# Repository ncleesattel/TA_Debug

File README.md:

# TA_Debug
PCB designed with KiCad to make a debug main unit for TeenAstro V3 testing.  
I haven't built my own debug platform yet, so I would encourage you to wait for my feedback.  

## internal connectors
The pcb is intended to accommodate:
* TMC5160 for RA, DEC and Focusser
  * the TMC5160 can either be connected via step/dir or SPI 
* 16 MHz oscillators for TMC5160
* NEO-M8n GNSS satellite positioning system
* DS3232 RTC
* power is supplied from a DC jack that splits into
  * VCC for steppers (12 - 24V)
  * 5V for legacy SHC
  * 3.3V for everything else
  * CR32 battery
* power is provided by two Traco DC/DC converters

## external connectors
An MCU like ESP32 or Teensy 4.x can be connected through a ribbon cable to a breadboard.  
There are also connectors for an SHC, stepper motors and encoders.  

## pictures

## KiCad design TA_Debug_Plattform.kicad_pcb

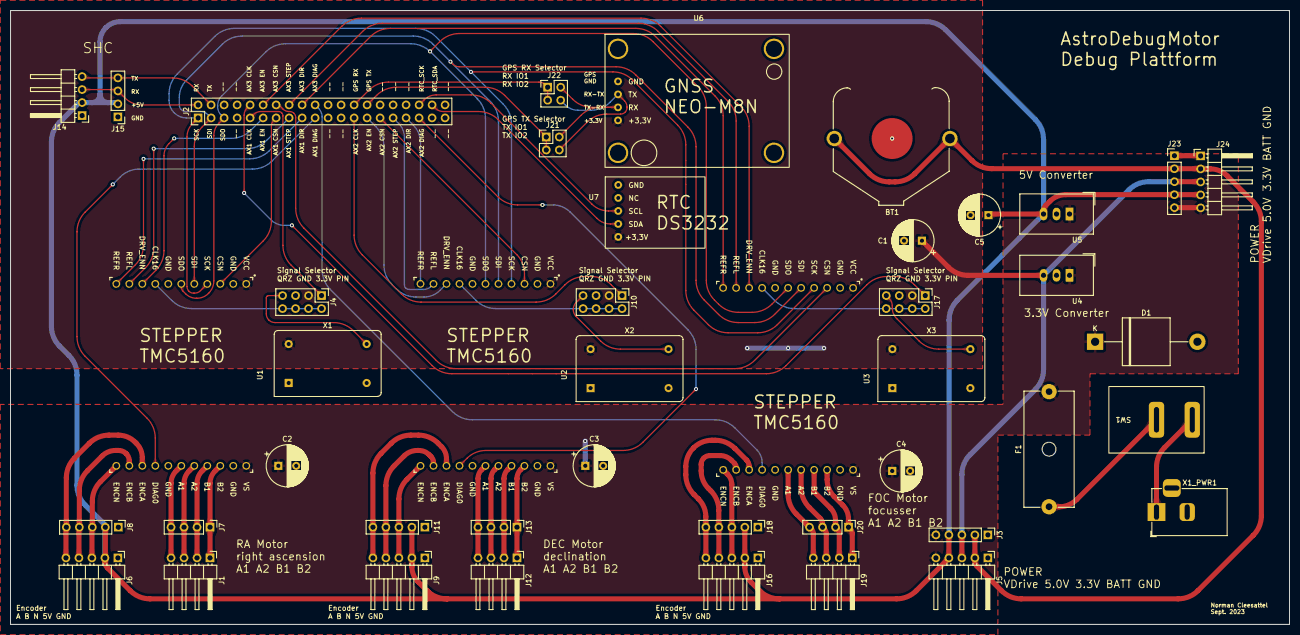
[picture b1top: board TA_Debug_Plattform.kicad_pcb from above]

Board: 2 copper layers, 250.0 x 120.0 mm, 44 parts (0 on the bottom side), 63 nets.

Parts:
BT1: CR2032-BS-6-1; Battery_KZH_20P
C1, C2, C3, C4, C5: 150uF; CP_Radial_D8.0mm_P3.50mm
D1: P600S; D_P600_R-6_P20.00mm_Horizontal
F1: FLINK 4,0A; Fuseholder_Cylinder-5x20mm_Schurter_0031_8201_Horizontal_Op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
J1: Motor A; PinHeader_1x04_P2.54mm_Horizontal
J2: Conn_02x20_Odd_Even; PinHeader_2x20_P2.54mm_Vertical
J3, J8, J11, J18, J23: Conn_01x05; PinHeader_1x05_P2.54mm_Vertical
J4: AX1 CLK SEL; PinHeader_2x04_P2.54mm_Vertical
J5, J6, J9, J16, J24: Conn_01x05; PinHeader_1x05_P2.54mm_Horizontal
J7: Motor A; PinHeader_1x04_P2.54mm_Vertical
J10: AX2 CLK SEL; PinHeader_2x04_P2.54mm_Vertical
J12: Motor B; PinHeader_1x04_P2.54mm_Horizontal
J13: Motor B; PinHeader_1x04_P2.54mm_Vertical
J14: SHC; PinHeader_1x04_P2.54mm_Horizontal
J15: SHC; PinHeader_1x04_P2.54mm_Vertical
J17: AX3 CLK SEL; PinHeader_2x04_P2.54mm_Vertical
J19: Motor C; PinHeader_1x04_P2.54mm_Horizontal
J20: Motor C; PinHeader_1x04_P2.54mm_Vertical
J21, J22: Conn_02x02_Odd_Even; PinHeader_2x02_P2.54mm_Vertical
SW1: SW_SPST; Marquart
U1, U2, U3: TMC5160-BOB; 22pin1,5x1,1-BOB
U4, U5: TSR_2-2450; Converter_DCDC_TRACO_TSR-2_THT
U6: NEO-M8n-GPS
U7: DS3232
X1, X2, X3: ACO-16MHz; Oscillator_DIP-14
X1_PWR1: Barrel_Jack_MountingPin; BarrelJack_Horizontal

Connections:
+3.3V: C1.1, J3.3, J4.3, J5.3, J10.3, J17.3, J23.3, J24.3, U1.1 (VCC-(3.3V/5V)), U2.1 (VCC-(3.3V/5V)), U3.1 (VCC-(3.3V/5V)), U4.3 (Vout), U6.4 (+3,3V), U7.1 (+3,3V), X1.14 (Vcc), X2.14 (Vcc), X3.14 (Vcc)
+5V: C5.1, J3.4, J5.4, J6.2, J8.2, J9.2, J11.2, J14.2, J15.2, J16.2, J18.2, J23.4, J24.4, U5.3 (Vout)
+BATT: BT1.1 (+), J3.2, J5.2, J23.2, J24.2
/AX1_A1: J1.4, J7.4, U1.17 (A1)
/AX1_A2: J1.3, J7.3, U1.16 (A2)
/AX1_B1: J1.2, J7.2, U1.15 (B1)
/AX1_B2: J1.1, J7.1, U1.14 (B2)
/AX1_CLK: J2.9, J4.1
/AX1_CSN: J2.13, U1.3 (CSN)
/AX1_DIAG: J2.19, U1.19 (DIAGO)
/AX1_DIR: J2.17, U1.11 (REFR)
/AX1_EN: J2.11, U1.9 (DRV_ENN)
/AX1_ENCA: J6.5, J8.5, U1.20 (ENCA)
/AX1_ENCB: J6.4, J8.4, U1.21 (ENCB)
/AX1_ENCN: J6.3, J8.3, U1.22 (ENCN)
/AX1_STEP: J2.15, U1.10 (REFL)
/AX2_A1: J12.4, J13.4, U2.17 (A1)
/AX2_A2: J12.3, J13.3, U2.16 (A2)
/AX2_B1: J12.2, J13.2, U2.15 (B1)
/AX2_B2: J12.1, J13.1, U2.14 (B2)
/AX2_CLK: J2.25, J10.1
/AX2_CSN: J2.29, U2.3 (CSN)
/AX2_DIAG: J2.35, U2.19 (DIAGO)
/AX2_DIR: J2.33, U2.11 (REFR)
/AX2_EN: J2.27, U2.9 (DRV_ENN)
/AX2_ENCA: J9.5, J11.5, U2.20 (ENCA)
/AX2_ENCB: J9.4, J11.4, U2.21 (ENCB)
/AX2_ENCN: J9.3, J11.3, U2.22 (ENCN)
/AX2_STEP: J2.31, U2.10 (REFL)
/AX3_A1: J19.4, J20.4, U3.17 (A1)
/AX3_A2: J19.3, J20.3, U3.16 (A2)
/AX3_B1: J19.2, J20.2, U3.15 (B1)
/AX3_B2: J19.1, J20.1, U3.14 (B2)
/AX3_CLK: J2.10, J17.1
/AX3_CSN: J2.14, U3.3 (CSN)
/AX3_DIAG: J2.20, U3.19 (DIAGO)
/AX3_DIR: J2.18, U3.11 (REFR)
/AX3_EN: J2.12, U3.9 (DRV_ENN)
/AX3_ENCA: J16.5, J18.5, U3.20 (ENCA)
/AX3_ENCB: J16.4, J18.4, U3.21 (ENCB)
/AX3_ENCN: J16.3, J18.3, U3.22 (ENCN)
/AX3_STEP: J2.16, U3.10 (REFL)
/GPS_RX: J2.26, J22.1, J22.3
/GPS_TX: J2.28, J21.1, J21.3
/IO1 GPS: J21.2, J22.2, U6.3 (RX)
/IO2 GPS: J21.4, J22.4, U6.2 (TX)
/RTC_SCK: J2.36, U7.3 (SCK)
/RTC_SDA: J2.38, U7.2 (SDA)
/RX: J2.2, J14.3, J15.3
/SCK: J2.1, U1.4 (SCK), U2.4 (SCK), U3.4 (SCK)
/SDI: J2.3, U1.5 (SDI), U2.5 (SDI), U3.5 (SDI)
/SDO: J2.5, U1.6 (SDO), U2.6 (SDO), U3.6 (SDO)
/TX: J2.4, J14.4, J15.4
GND: BT1.2 (-), C1.2, C2.2, C3.2, C4.2, C5.2, D1.2 (A), J3.1, J4.5, J5.1, J6.1, J8.1, J9.1, J10.5, J11.1, J14.1, J15.1, J16.1, J17.5, J18.1, J23.1, J24.1, U1.2 (GND), U1.7 (GND), U1.13 (GND), U1.18 (GND), U2.2 (GND), U2.7 (GND), U2.13 (GND), U2.18 (GND), U3.2 (GND), U3.7 (GND), U3.13 (GND), U3.18 (GND), U4.2 (GND), U5.2 (GND), U6.1 (GND), U6.5 (GND), U7.4 (NC), U7.5 (GND), X1.7 (GND), X1_PWR1.2, X2.7 (GND), X3.7 (GND)
unnamed: J4.2, J4.4, J4.6, J4.8, U1.8 (CLK16)
unnamed: J4.7, X1.8 (OUT)
unnamed: J10.2, J10.4, J10.6, J10.8, U2.8 (CLK16)
unnamed: J10.7, X2.8 (OUT)
unnamed: J17.2, J17.4, J17.6, J17.8, U3.8 (CLK16)
unnamed: J17.7, X3.8 (OUT)
unnamed: SW1.1 (A), X1_PWR1.1
unnamed: F1.1, SW1.2 (B)
Vdrive: C2.1, C3.1, C4.1, D1.1 (K), F1.2, J3.5, J5.5, J23.5, J24.5, U1.12 (VS-(9-36V)), U2.12 (VS-(9-36V)), U3.12 (VS-(9-36V)), U4.1 (Vin), U5.1 (Vin)

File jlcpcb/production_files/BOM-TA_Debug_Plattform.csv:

Comment,Designator,Footprint,LCSC
ACO-16MHz,X3,Oscillator_DIP-14,
TMC5160-BOB,U3,"22pin1,5x1,1-BOB",
Motor C,J20,PinHeader_1x04_P2.54mm_Vertical,
Motor C,J19,PinHeader_1x04_P2.54mm_Horizontal,
Conn_01x05,J18,PinHeader_1x05_P2.54mm_Vertical,
AX3 CLK SEL,J17,PinHeader_2x04_P2.54mm_Vertical,
Conn_01x05,J16,PinHeader_1x05_P2.54mm_Horizontal,
SHC,J14,PinHeader_1x04_P2.54mm_Horizontal,
150uF,C4,CP_Radial_D8.0mm_P3.50mm,
150uF,C1,CP_Radial_D8.0mm_P3.50mm,
SW_SPST,SW1,Marquart,
P600S,D1,D_P600_R-6_P20.00mm_Horizontal,
Conn_01x05,J5,PinHeader_1x05_P2.54mm_Horizontal,
ACO-16MHz,X2,Oscillator_DIP-14,
TSR_2-2450,U4,Converter_DCDC_TRACO_TSR-2_THT,
Conn_01x05,J8,PinHeader_1x05_P2.54mm_Vertical,
"FLINK 4,0A",F1,Fuseholder_Cylinder-5x20mm_Schurter_0031_8201_Horizontal_Open,
ACO-16MHz,X1,Oscillator_DIP-14,
Conn_01x05,J11,PinHeader_1x05_P2.54mm_Vertical,
AX1 CLK SEL,J4,PinHeader_2x04_P2.54mm_Vertical,
150uF,C2,CP_Radial_D8.0mm_P3.50mm,
Conn_01x05,J6,PinHeader_1x05_P2.54mm_Horizontal,
Conn_01x05,J9,PinHeader_1x05_P2.54mm_Horizontal,
Motor A,J7,PinHeader_1x04_P2.54mm_Vertical,
Barrel_Jack_MountingPin,X1_PWR1,BarrelJack_Horizontal,
TSR_2-2450,U5,Converter_DCDC_TRACO_TSR-2_THT,
Motor A,J1,PinHeader_1x04_P2.54mm_Horizontal,
Conn_01x05,J3,PinHeader_1x05_P2.54mm_Vertical,
Motor B,J13,PinHeader_1x04_P2.54mm_Vertical,
Motor B,J12,PinHeader_1x04_P2.54mm_Horizontal,
SHC,J15,PinHeader_1x04_P2.54mm_Vertical,
TMC5160-BOB,U2,"22pin1,5x1,1-BOB",
TMC5160-BOB,U1,"22pin1,5x1,1-BOB",
AX2 CLK SEL,J10,PinHeader_2x04_P2.54mm_Vertical,
150uF,C3,CP_Radial_D8.0mm_P3.50mm,
Conn_02x20_Odd_Even,J2,PinHeader_2x20_P2.54mm_Vertical,
Conn_01x05,J24,PinHeader_1x05_P2.54mm_Horizontal,
Conn_01x05,J23,PinHeader_1x05_P2.54mm_Vertical,
CR2032-BS-6-1,BT1,Battery_KZH_20P,
Conn_02x02_Odd_Even,J22,PinHeader_2x02_P2.54mm_Vertical,
Conn_02x02_Odd_Even,J21,PinHeader_2x02_P2.54mm_Vertical,
NEO-M8n-GPS,U6,NEO-M8n-GPS,
150uF,C5,CP_Radial_D8.0mm_P3.50mm,
~,U7,DS3232,

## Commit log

2023-09-29 Initial upload
2023-09-29 add pictures
2023-09-29 PDF of scheme
